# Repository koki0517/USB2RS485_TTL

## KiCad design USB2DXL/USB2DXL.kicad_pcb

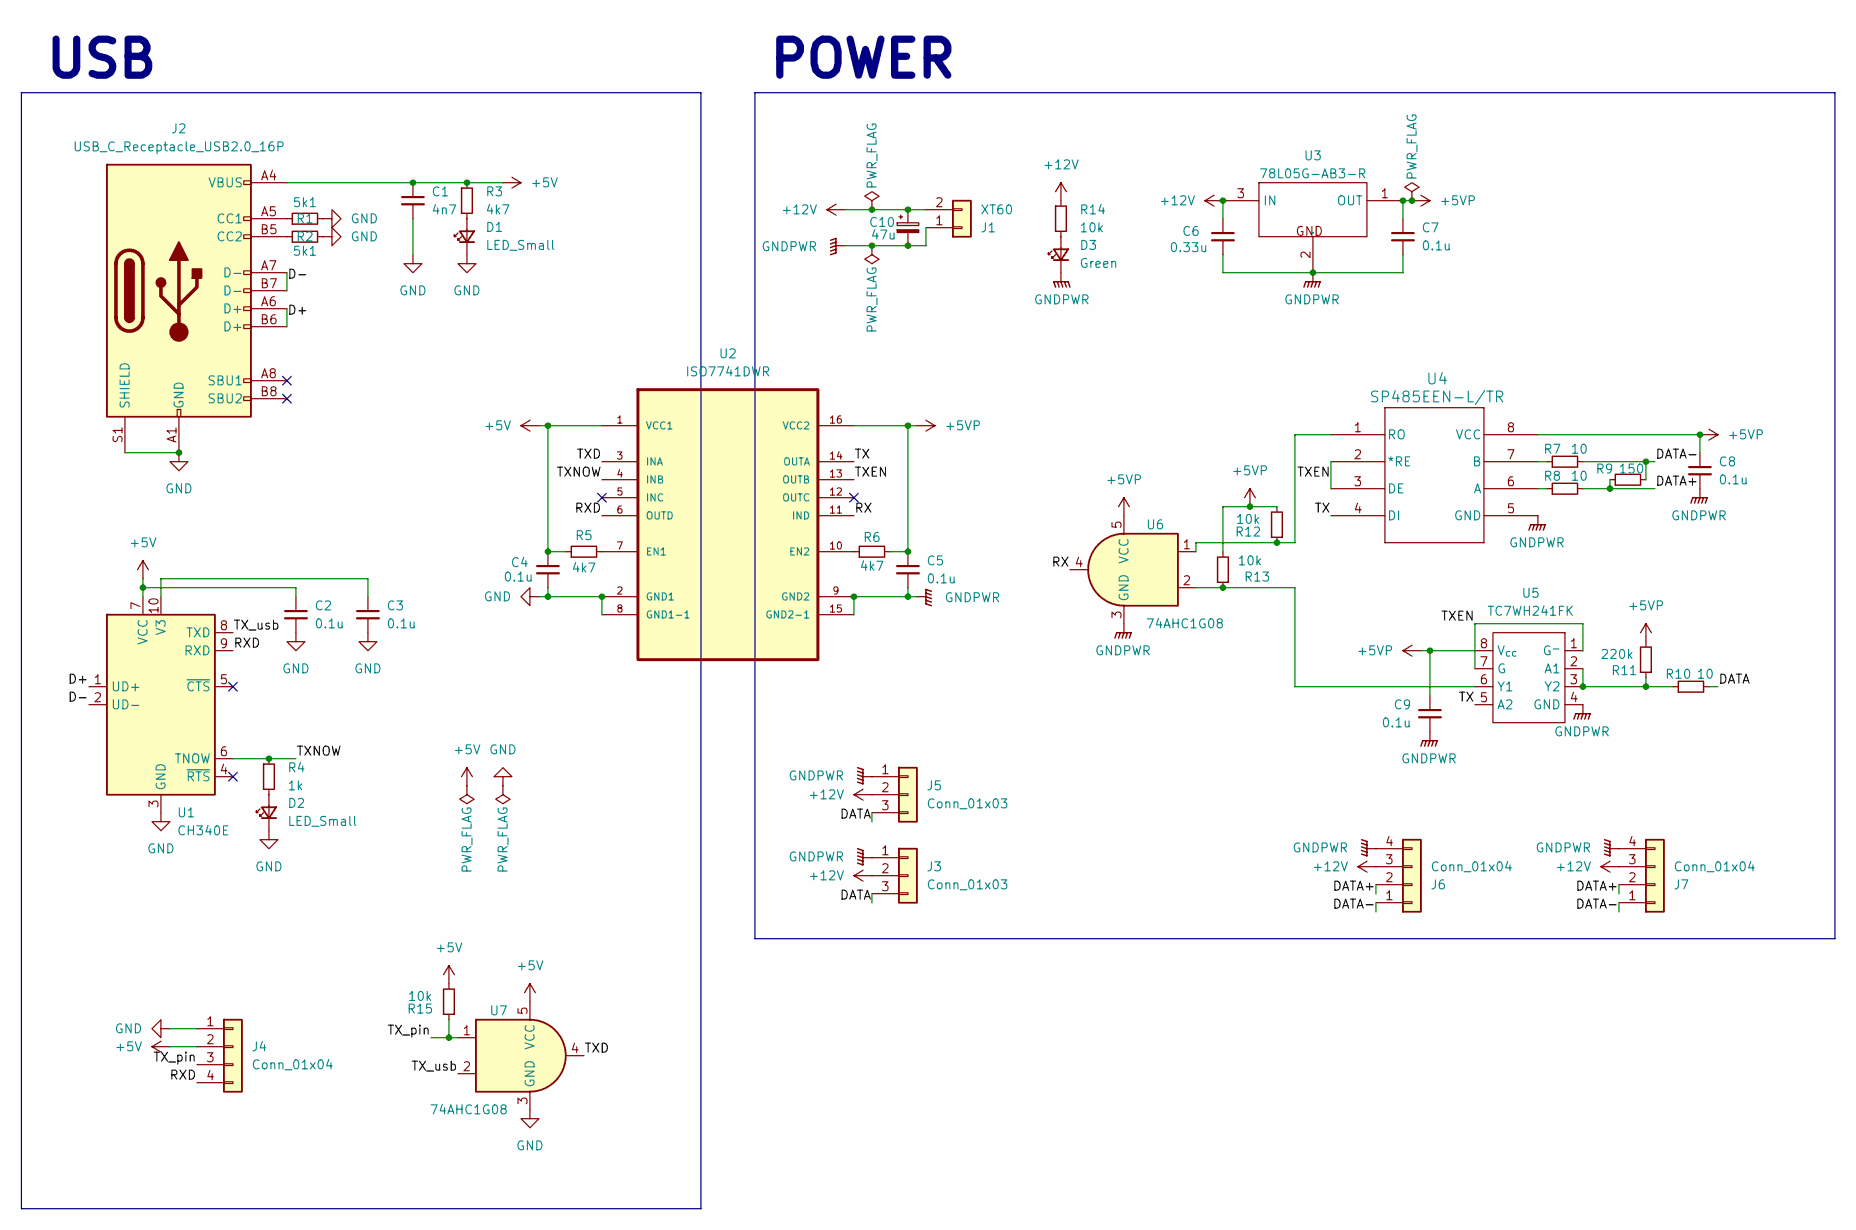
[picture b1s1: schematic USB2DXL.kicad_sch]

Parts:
C1: 4n7; C_0402_1005Metric
C2, C3, C4, C5, C7, C8, C9: 0.1u; C_0402_1005Metric
C6: 0.33u; C_0603_1608Metric
C10: 47u; CP_Radial_D5.0mm_P2.00mm
D1, D2: LED_Small; LED_0603_1608Metric
D3: Green; LED_0805_2012Metric_Pad1.15x1.40mm_HandSolder
J1: XT60; AMASS_XT60-F_1x02_P7.20mm_Vertical
J2: USB_C_Receptacle_USB2.0_16P; USB_C_Receptacle_HRO_TYPE-C-31-M-12
J3, J5: Conn_01x03; JST_EH_B3B-EH-A_1x03_P2.50mm_Vertical
J4: Conn_01x04; JST_XA_B04B-XASK-1_1x04_P2.50mm_Vertical
J6, J7: Conn_01x04; Molex_SPOX_5267-04A_1x04_P2.50mm_Vertical
R1, R2: 5k1; R_0402_1005Metric
R3, R5, R6: 4k7; R_0402_1005Metric
R4: 1k; R_0402_1005Metric
R7, R8, R10: 10; R_0402_1005Metric
R9: 150; R_0402_1005Metric
R11: 220k; R_0402_1005Metric
R12, R14, R15: 10k; R_0402_1005Metric
R13: 10k; C_0402_1005Metric
U1: CH340E; MSOP-10_3x3mm_P0.5mm
U2: ISO7741DWR; SOIC127P1030X265-16N
U3: 78L05G-AB3-R; SOT-89-3; Manufacturer Part 78L05G-AB3-R; LCSC Part Name 输入30V 输出5V 100mA
U4: SP485EEN-L/TR; NSOIC-8
U5: TC7WH241FK; VSSOP-8_2.3x2mm_P0.5mm
U6, U7: 74AHC1G08; SOT-23-5_HandSoldering

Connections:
+5V: C1.1, C2.1, C4.1, J2.A4 (VBUS), J2.A9 (VBUS), J2.B4 (VBUS), J2.B9 (VBUS), J4.2, R3.1, R5.1, R15.2, U1.7 (VCC), U2.1 (VCC1), U7.5 (VCC)
+5VP: C5.1, C7.1, C8.1, C9.1, R6.2, R11.2, R12.2, R13.2, U2.16 (VCC2), U3.1 (OUT), U4.8 (VCC), U5.8 (V_{cc}), U6.5 (VCC)
+12V: C6.1, C10.1, J1.2, J3.2, J5.2, J6.3, J7.3, R14.1, U3.3 (IN)
/D+: J2.A6 (D+), J2.B6 (D+), U1.1 (UD+)
/D-: J2.A7 (D-), J2.B7 (D-), U1.2 (UD-)
/DATA: J3.3, J5.3, R10.2
/DATA+: J6.2, J7.2, R8.2, R9.1
/DATA-: J6.1, J7.1, R7.2, R9.2
/RX: U2.11 (IND), U6.4
/RXD: J4.4, U1.9 (RXD), U2.6 (OUTD)
/TX: U2.14 (OUTA), U4.4 (DI), U5.5 (A2)
/TXD: U2.3 (INA), U7.4
/TXEN: U2.13 (OUTB), U4.2 (*RE), U4.3 (DE), U5.1 (G^{-}), U5.7 (G)
/TXNOW: R4.1, U1.6 (TNOW), U2.4 (INB)
/TX_pin: J4.3, R15.1, U7.1
/TX_usb: U1.8 (TXD), U7.2
GND: C1.2, C2.2, C3.2, C4.2, D1.1 (K), D2.1 (K), J2.A1 (GND), J2.A12 (GND), J2.B1 (GND), J2.B12 (GND), J2.S1 (SHIELD), J4.1, R1.2, R2.2, U1.3 (GND), U2.2 (GND1), U2.8 (GND1-1), U7.3 (GND)
GNDPWR: C5.2, C6.2, C7.2, C8.2, C9.2, C10.2, D3.1 (K), J1.1, J3.1, J5.1, J6.4, J7.4, U2.9 (GND2), U2.15 (GND2-1), U3.2 (GND), U4.5 (GND), U5.4 (GND), U6.3 (GND)
unnamed: D1.2 (A), R3.2
unnamed: D2.2 (A), R4.2
unnamed: D3.2 (A), R14.2
unnamed: J2.A5 (CC1), R1.1
unnamed: J2.B5 (CC2), R2.1
unnamed: C3.1, U1.10 (V3)
unnamed: R5.2, U2.7 (EN1)
unnamed: R6.1, U2.10 (EN2)
unnamed: R8.1, U4.6 (A)
unnamed: R7.1, U4.7 (B)
unnamed: R12.1, U4.1 (RO), U6.1
unnamed: R10.1, R11.1, U5.2 (A1), U5.3 (Y2)
unnamed: R13.1, U5.6 (Y1), U6.2

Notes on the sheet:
USB
POWER

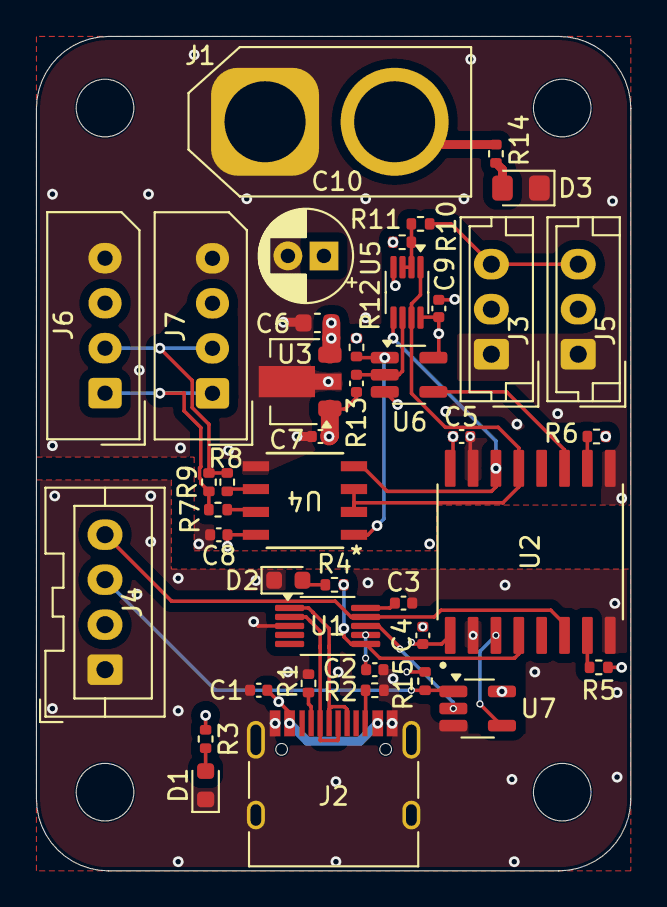
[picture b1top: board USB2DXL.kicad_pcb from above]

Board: 4 copper layers, 33.0 x 46.4 mm, 42 parts (0 on the bottom side), 31 nets.

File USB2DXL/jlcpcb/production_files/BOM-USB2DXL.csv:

Comment,Designator,Footprint,LCSC,Quantity
1k,R4,R_0402_1005Metric,C11702,1
0.1u,"C2,C3,C4,C5,C7,C8,C9",C_0402_1005Metric,C1525,7
4n7,C1,C_0402_1005Metric,C1538,1
0.33u,C6,C_0603_1608Metric,C1615,1
LED_Small,D1,LED_0603_1608Metric,C2286,1
LED_Small,D2,LED_0603_1608Metric,C2290,1
Green,D3,LED_0805_2012Metric_Pad1.15x1.40mm_HandSolder,C2297,1
10,"R10,R7,R8",R_0402_1005Metric,C25077,3
150,R9,R_0402_1005Metric,C25082,1
10k,"R12,R13,R14,R15",R_0402_1005Metric,C25744,4
220k,R11,R_0402_1005Metric,C25767,1
4k7,"R3,R5,R6",R_0402_1005Metric,C25900,3
5k1,"R1,R2",R_0402_1005Metric,C25905,2
USB_C_Receptacle_USB2.0_16P,J2,USB_C_Receptacle_HRO_TYPE-C-31-M-12,C393939,1
ISO7741DWR,U2,SOIC127P1030X265-16N,C571196,1
SP485EEN-L/TR,U4,NSOIC-8,C6855,1
78L05G-AB3-R,U3,SOT-89-3,C71136,1
74AHC1G08,"U6,U7",SOT-23-5_HandSoldering,C7467,2
CH340E,U1,MSOP-10_3x3mm_P0.5mm,C99652,1
Conn_01x03,J3,JST_EH_B3B-EH-A_1x03_P2.50mm_Vertical,,1
Conn_01x03,J5,JST_EH_B3B-EH-A_1x03_P2.50mm_Vertical,,1
Conn_01x04,J6,Molex_SPOX_5267-04A_1x04_P2.50mm_Vertical,,1
TC7WH241FK,U5,VSSOP-8_2.3x2mm_P0.5mm,,1
XT60,J1,AMASS_XT60-F_1x02_P7.20mm_Vertical,,1
Conn_01x04,J7,Molex_SPOX_5267-04A_1x04_P2.50mm_Vertical,,1
47u,C10,CP_Radial_D5.0mm_P2.00mm,,1
Conn_01x04,J4,JST_XA_B04B-XASK-1_1x04_P2.50mm_Vertical,,1

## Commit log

2025-07-06 hoge
2025-07-08 パターンを引いた
2025-07-08 pdfの追加
2025-07-19 D+とD-逆だったちね
2025-08-03 マイコンからのUARTで動かせるようにした
